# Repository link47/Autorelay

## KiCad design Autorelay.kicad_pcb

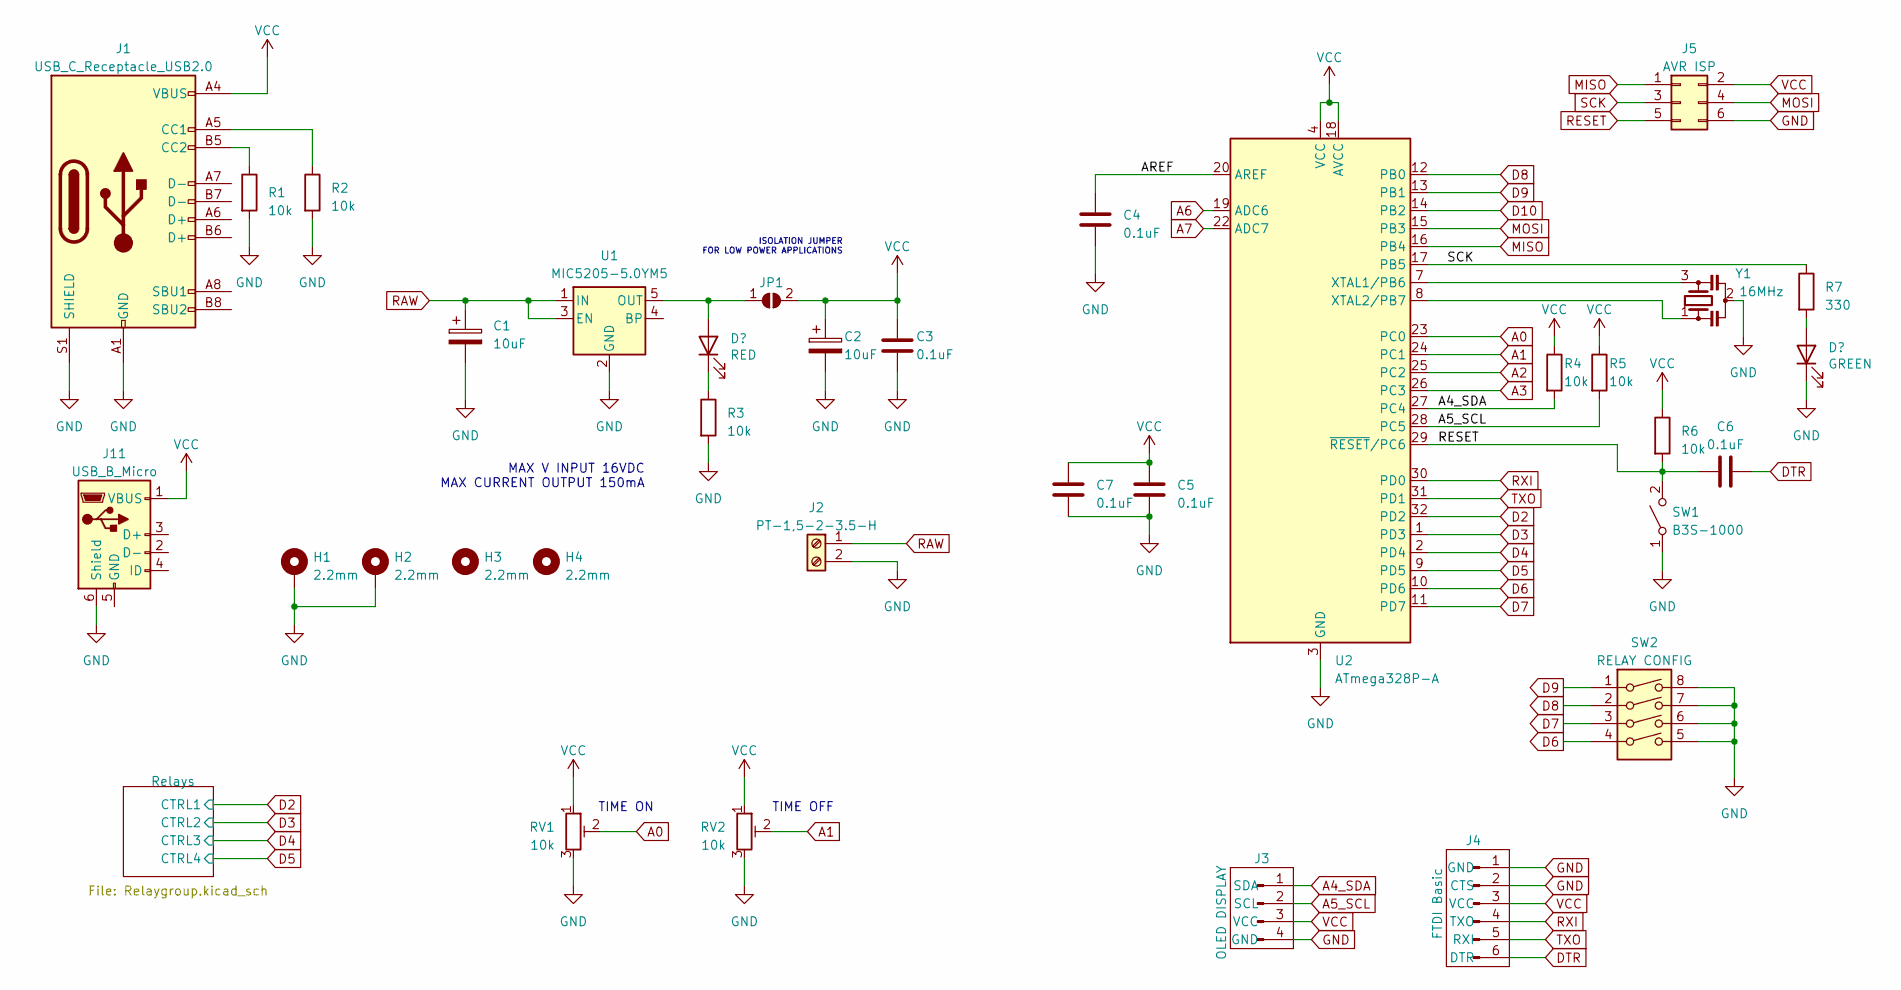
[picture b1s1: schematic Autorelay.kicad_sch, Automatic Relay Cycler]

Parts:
C1, C2: 10uF; C_1206_3216Metric; LCSC F931C106MAA
C3, C4, C5, C6, C7: 0.1uF; C_0603_1608Metric
D1: RED; LED_0805_2012Metric; LCSC C84256
D2: GREEN; LED_0805_2012Metric; LCSC C2297
H1, H2: 2.2mm; MountingHole_2.2mm_M2_DIN965_Pad
H3, H4: 2.2mm; MountingHole_2.2mm_M2_DIN965
J1: USB_C_Receptacle_USB2.0; TYPE-C-31-M-14; LCSC TYPE-C-31-M-14
J2: PT-1,5-2-3.5-H; TerminalBlock_Phoenix_PT-1,5-2-3.5-H_1x02_P3.50mm_Horizontal
J3: OLED DISPLAY; PinHeader_1x04_P2.54mm_Vertical
J4: FTDI Basic; PinHeader_1x06_P2.54mm_Vertical
J5: AVR ISP; PinHeader_2x03_P2.54mm_Vertical
J11: USB_B_Micro; USB_Micro-B_GCT_USB3076-30-A
JP1: SolderJumper_2_Open; SolderJumper-2_P1.3mm_Open_Pad1.0x1.5mm
R1, R2, R3, R4, R5, R6: 10k; R_0603_1608Metric
R7: 330; R_0603_1608Metric
RV1, RV2: 10k; Potentiometer_Bourns_TC33X_Vertical; LCSC C719176
SW1: B3S-1000; SW_SPST_B3S-1000; LCSC C180420
SW2: RELAY CONFIG; SW_DIP_SPSTx04_Slide_Omron_A6S-410x_W8.9mm_P2.54mm; LCSC C306873
U1: MIC5205-5.0YM5; SOT-23-5; LCSC C70431
U2: ATmega328P-A; TQFP-32_7x7mm_P0.8mm; LCSC C14877
Y1: 16MHz; Resonator_SMD_Murata_CSTxExxV-3Pin_3.0x1.1mm; LCSC C341521

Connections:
/AREF: C4.1, U2.20 (AREF)
A0: RV1.2, U2.23 (PC0)
A1: RV2.2, U2.24 (PC1)
A2: U2.25 (PC2)
A3: U2.26 (PC3)
A4_SDA: J3.1 (SDA), R4.2, U2.27 (PC4)
A5_SCL: J3.2 (SCL), R5.2, U2.28 (PC5)
A6: U2.19 (ADC6)
A7: U2.22 (ADC7)
D2: U2.32 (PD2); also elsewhere on the board
D3: U2.1 (PD3); also elsewhere on the board
D4: U2.2 (PD4); also elsewhere on the board
D5: U2.9 (PD5); also elsewhere on the board
D6: SW2.4, U2.10 (PD6)
D7: SW2.3, U2.11 (PD7)
D8: SW2.2, U2.12 (PB0)
D9: SW2.1, U2.13 (PB1)
D10: U2.14 (PB2)
DTR: C6.2, J4.6 (DTR)
GND: C1.2, C2.2, C3.2, C4.2, C5.2, C7.2, D2.1 (K), H1.1, H2.1, J1.A1 (GND), J1.A12 (GND), J1.B1 (GND), J1.B12 (GND), J1.S1 (SHIELD), J2.2, J3.4 (GND), J4.1 (GND), J4.2 (CTS), J5.6, J11.6 (Shield), R1.2, R2.2, R3.2, RV1.3, RV2.3, SW1.1 (A), SW2.5, SW2.6, SW2.7, SW2.8, U1.2 (GND), U2.3 (GND), U2.5 (GND), U2.21 (GND), Y1.2; also elsewhere on the board
MISO: J5.1, U2.16 (PB4)
MOSI: J5.4, U2.15 (PB3)
unnamed: D1.2 (A), JP1.1 (A), U1.5 (OUT)
unnamed: D1.1 (K), R3.1
unnamed: D2.2 (A), R7.2
unnamed: J1.A5 (CC1), R2.1
unnamed: J1.B5 (CC2), R1.1
unnamed: U2.7 (XTAL1/PB6), Y1.3
unnamed: U2.8 (XTAL2/PB7), Y1.1
RAW: C1.1, J2.1, U1.1 (IN), U1.3 (EN)
RESET: C6.1, J5.5, R6.2, SW1.2 (B), U2.29 (~RESET/PC6)
RXI: J4.4 (TXO), U2.30 (PD0)
SCK: J5.3, R7.1, U2.17 (PB5)
TXO: J4.5 (RXI), U2.31 (PD1)
VCC: C2.1, C3.1, C5.1, C7.1, J1.A4 (VBUS), J1.A9 (VBUS), J1.B4 (VBUS), J1.B9 (VBUS), J3.3 (VCC), J4.3 (VCC), J5.2, J11.1 (VBUS), JP1.2 (B), R4.1, R5.1, R6.1, RV1.1, RV2.1, U2.4 (VCC), U2.6 (VCC), U2.18 (AVCC); also elsewhere on the board

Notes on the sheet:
TIME ON
ISOLATION JUMPER FOR LOW POWER APPLICATIONS
TIME OFF
MAX V INPUT 16VDC MAX CURRENT OUTPUT 150mA

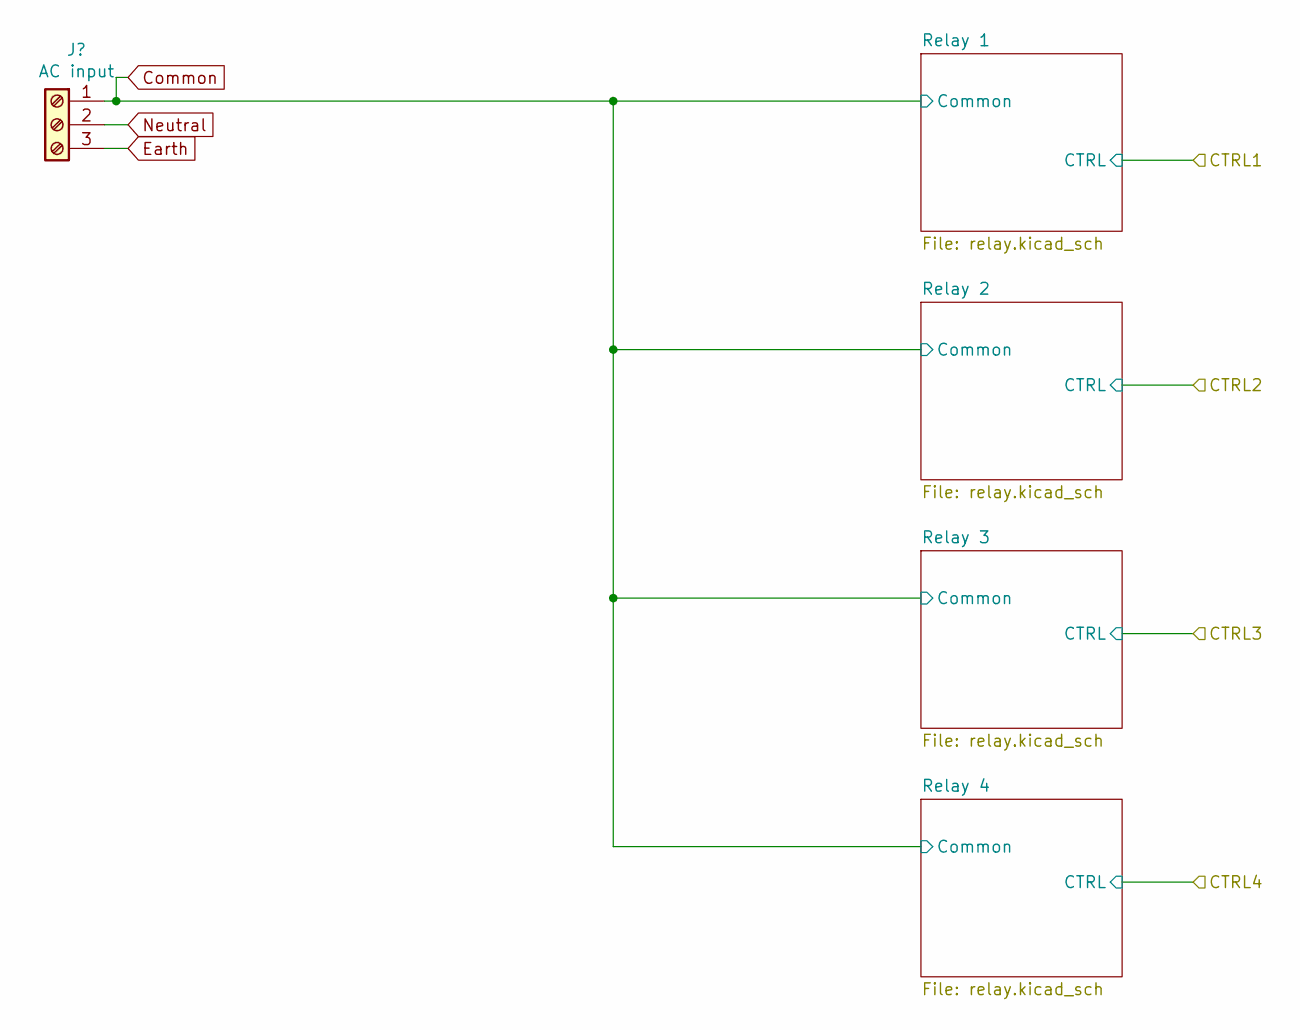
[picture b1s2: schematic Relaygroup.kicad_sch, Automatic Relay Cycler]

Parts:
J6: AC input; TerminalBlock_Phoenix_MKDS-1,5-3-5.08_1x03_P5.08mm_Horizont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

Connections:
Common: J6.1; also elsewhere on the board
Earth: J6.3; also elsewhere on the board
Neutral: J6.2; also elsewhere on the board

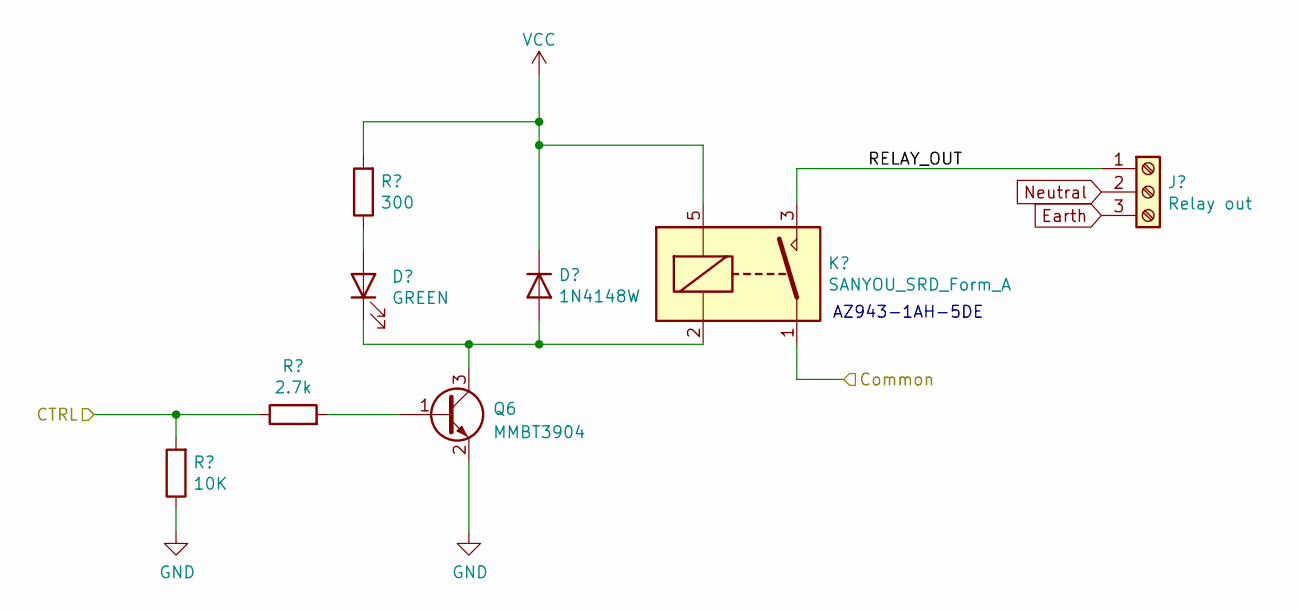
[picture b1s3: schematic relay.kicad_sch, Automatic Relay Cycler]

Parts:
D3: GREEN; LED_0805_2012Metric; LCSC C2297
D4: 1N4148W; D_SOD-123; LCSC C83528
J7: Relay out; TerminalBlock_Phoenix_MKDS-1,5-3-5.08_1x03_P5.08mm_Horizont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
K1: SANYOU_SRD_Form_A; Relay_SPST_SANYOU_SRD_Series_Form_A
Q6: MMBT3904; SOT-23; LCSC C20526
R8: 10K; R_0603_1608Metric
R9: 2.7k; R_0603_1608Metric
R10: 300; R_0603_1608Metric

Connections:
/Relays/Relay 1/RELAY_OUT: J7.1, K1.3
Common: K1.1; also elsewhere on the board
D2: R8.2, R9.1; also elsewhere on the board
Earth: J7.3; also elsewhere on the board
GND: Q6.2 (E), R8.1; also elsewhere on the board
unnamed: D3.2 (A), R10.1
Neutral: J7.2; also elsewhere on the board
VCC: D4.1 (K), K1.5, R10.2; also elsewhere on the board

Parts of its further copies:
D5, D7, D9: GREEN; LED_0805_2012Metric; LCSC C2297
D6, D8, D10: 1N4148W; D_SOD-123; LCSC C83528
J8, J9, J10: Relay out; TerminalBlock_Phoenix_MKDS-1,5-3-5.08_1x03_P5.08mm_Horizont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
K2, K3, K4: SANYOU_SRD_Form_A; Relay_SPST_SANYOU_SRD_Series_Form_A
Q5, Q7, Q8: MMBT3904; SOT-23; LCSC C20526
R11, R14, R17: 10K; R_0603_1608Metric
R12, R15, R18: 2.7k; R_0603_1608Metric
R13, R16, R19: 300; R_0603_1608Metric

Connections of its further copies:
/Relays/Relay 2/RELAY_OUT: J8.1, K2.3
/Relays/Relay 3/RELAY_OUT: J9.1, K3.3
/Relays/Relay 4/RELAY_OUT: J10.1, K4.3
Common: K2.1, K3.1, K4.1; also elsewhere on the board
D3: R11.2, R12.1; also elsewhere on the board
D4: R14.2, R15.1; also elsewhere on the board
D5: R17.2, R18.1; also elsewhere on the board
Earth: J8.3, J9.3, J10.3; also elsewhere on the board
GND: Q5.2 (E), Q7.2 (E), Q8.2 (E), R11.1, R14.1, R17.1; also elsewhere on the board
unnamed: D5.2 (A), R13.1
unnamed: D7.2 (A), R16.1
unnamed: D7.1 (K), D8.2 (A), K3.2, Q7.3 (C)
unnamed: D9.2 (A), R19.1
unnamed: D9.1 (K), D10.2 (A), K4.2, Q8.3 (C)
unnamed: Q7.1 (B), R15.2
unnamed: Q8.1 (B), R18.2
Neutral: J8.2, J9.2, J10.2; also elsewhere on the board
VCC: D6.1 (K), D8.1 (K), D10.1 (K), K2.5, K3.5, K4.5, R13.2, R16.2, R19.2; also elsewhere on the board

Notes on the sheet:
AZ943-1AH-5DE

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
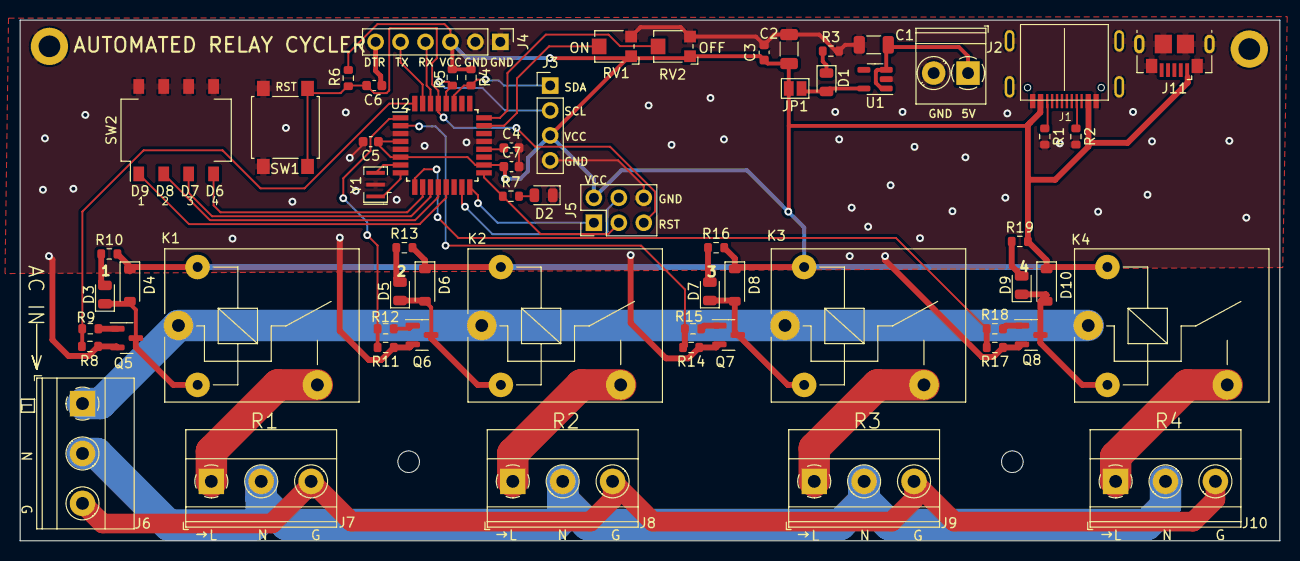
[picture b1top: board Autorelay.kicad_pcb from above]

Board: 2 copper layers, 128.3 x 53.0 mm, 67 parts (0 on the bottom side), 49 nets.

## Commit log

2023-03-09 add code
2023-03-14 display updates
